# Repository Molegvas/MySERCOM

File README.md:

#          Адаптер силового блока зарядного устройства

##   Кратко 

Адаптер силового блока предназначен для соединения управляющего контроллера с силовым блоком. Центральный микроконтроллер освобождается от исполнения рутинных операций.

 ### Аппаратная поддержка
   Прототипирование выполнялось на плате SAMD21-M0-Mini. Подробности включения хорошо описаны в https://github.com/BLavery/SAMD21-M0-Mini.
  К сожалению поддержка Arduino не в полной мере соответствует потребностям проекта, но это преодолимо.

 #### Особенности прототипирования на плате SAMD21-M0-Mini
  В качестве инструкции:  https://github.com/BLavery/SAMD21-M0-Mini:
 * select the board: Tools/Board = Arduino SAMD / "Arduino Zero (Native USB Port)".
 * Double-click the board reset button. Upload. See if a LED blinks.
 explain a bit:
 1. The Arduino bootloader uses double click on reset button to enter flash upload mode. Single
    reset enters normal running mode.
 2. The serial/bossac mode of USB upload is included in the Arduino install.
 3. The regular user LED is missing. So we choose one of the TX/RX LEDs. For the moment, 
    the Arduino sketch is NOT otherwise driving these as TX/RX indicators (see above), 
    so we can re-employ them.
 4. But what pin or GPIO number? For this board, reference the pins as 0-26 or A0-A5. Not D25, 
    nor PB03 or PB3.

 ### Обмен между контроллерами.

*  Протокол WAKE является логическим уровнем интерфейса управления оборудованием с помощью асинхронного последовательного канала. Физический уровень интерфейса протоколом не определяется, может использоваться, например, RS-232, RS-485 или USB. Протокол позволяет производить обмен пакетами данных (data frames) длиной до 255 байт с адресуемыми устройствами, которых может быть до 127. Формат данных может быть любым. Могут передаваться байтовые поля, многобайтовые слова или строки символов. Для контроля правильности передачи данных используется контрольная сумма (CRC-8).
* Подробная информация о WAKE: http://leoniv.diod.club/articles/wake/wake.html
Выбор этого протокола объясняется тем, что хорошо известен автору и многолетней работой доказал свою надежность в устройстве ротации кондиционеров.
* Первоначальные планы использовать в качестве физического носителя SPI разбились о прозу жизни - в наличии не оказалось соответствующего адаптера USB-3SPI. Для целей прототипирования используется USB-UART терминал WakeUp! от Ридико Леонида Ивановича. Найдете в "resources".
* Передача параметров из нескольких байт: сначала старший, потом младшие.
* Время ожидания ответа ограничено 1000мс.  

 ### Управление измерениями.

 #### Измерение напряжения
   Измерение напряжения предполагается в диапазоне от -0,2В до +20,0В. Режим АЦП - дифференциальный. Опорное напряжение и усиление - выбор есть. Если получится реализовать вариант со сдвигом по напряжению на 200мВ минусовой клеммы, то обработка неправильной полярности подключения не потребует аппаратной поддержки. 

 #### Измерение тока
   Измерение тока в диапазоне от -16 до +16 ампер на токоизмерительном шунте укладывается в диапазон входного напряжения от -160 до +160мВ. Режим АЦП - дифференциальный. Пороги аварийного отключения не выставлялись.
 #### Измерение тока разряда
Зарезервировано. 
 #### Измерение температуры
Для датчика типа MF52 B 3950 NTC термистор 2% 10 kOm, последовательно резистор 10 kOm, запитан от 3,3в.
Параметры по умолчанию и задаваемые командой 0x57:

| bits | ref | gain | sampl | div | comp | offset | ser Ohm | nom Ohm |
|------|-----|------|-------|-----|------|--------|---------|---------|
|  01  |  00 |  00  |   03  |  04 |  00  |  0000  |  2710   |   2710  |

Ответ: код АЦП (2 байта) и значение температур, умноженное на 100.
Вычисления производятся по формуле Стейнхарта.

* Конфигурирование канала измерения состоит из параметров АЦП (разрядность, усреднение, см. страницы 853 и 862) и датчика (опорное напряжение, усиление, приборное смещение, коэффициент преобразования данных в физическую величину).
* В ответ контроллер отправляет пакет, содержащий байт ошибки (зарезервированная позиция), двухбайтный код АЦП и двухбайтное значение измеренной величины (для напряжения - в милливольтах).
* Команды такого типа скорее исследовательские, служащие для поиска оптимальных конфигураций.
* Выбор параметров, предложенных в datasheet ... как говорится, "не все йогурты одинаково полезны" ... 
* Аппаратное смещение задается отдельной командой, усиление - не исследовалось.      
* Ниже дано пояснение формата команды на примере конфигурирования измерителя напряжения.
```c++
// Настройка измерителя напряжения (код команды 0x55  'cmd_set_adc_bat')     
void doAdcBat()
{
    if( rxNbt == 10 )		  // Проверка получения полного пакета
  {
    uint8_t err           = 0x00;
    constexpr uint8_t prb = 0x00; // Измеритель напряжения, в [] - ориентировочные параметры
      // Задать все параметры измерителя [ 01 00 00 03 04 00 0000 12BA ]
    adcBits     [prb] = rxDat[0]; // Разрешение: 0x00(12), [0x01(16)], 0x02(10),  0x03(8)
    prbReference[prb] = rxDat[1]; // Опорное:   [0x00(1V)], 0x01(1/1.48VDDA),     0x02(1/2VDDA), 0x03(ExtA)
    prbGain     [prb] = rxDat[2]; // Усиление:  [0x00(X1)], 0x01(X2),  0x03(X4),  0x04(X8),      (X16), (DIV2)    
    adcSamples  [prb] = rxDat[3]; // Накопление: 0x00(1),   0x01(2),   0x02(4),  [0x03(8)],      0x04(16), ... 0x0a
    adcDivider  [prb] = rxDat[4]; // Делитель:   0x00(2^0), 0x01(2^1), 0x02(2^2), 0x03(2^3),    [0x04(2^4)]... 0x07
    refComp    = 0x01 & rxDat[5]; // 0/1: выкл/вкл аппаратное смещение АЦП
    prbOffset   [prb] = get16(6); // Приборное смещение: 0x8000 ... 0x7fff
    prbDivider  [prb] = get16(8); // Коэффициент преобразования в милливольты:   [0x12ba]
      // Считать результат
                                          // Нулевой байт - ошибка параметра (зарезервировано)
    txDat[1] = ( adcVoltage >> 8) & 0xFF; // Hi
    txDat[2] =   adcVoltage       & 0xFF; // Lo
    txDat[3] = ( voltage >> 8)    & 0xFF; // Hi
    txDat[4] =   voltage          & 0xFF; // Lo

    txReplay( 5, err );		  // Ответ из 5 байт
  }
  else
  {
    txReplay(1, err_tx);	  // Передается код ошибки протокола
  }
}
```

 ### Управление процессами
   Управление производится через два регистра состояния (они же и регистры управления)
 #### state1
* _switchStatus          - управление коммутатором в цепи плюсовой клеммы (foff_pin)
* _converterStatus       - управление преобразователем UC3845
* _currentControlStatus  - пид-регулирование по току
* _voltageControlStatus  - пид-регулирование по напряжению
* _chargeStatus          - управление переключением аналогового выхода на заряд или разряд
* _dischargeStatus       - состояние заряд/разряд
* _pauseStatus           - пауза
* _pidStatus        	 - управление регулятором

 #### state2
* _overHeatingStatus     - состояние перегрева
* _overloadStatus        - состояние перегрузки
* _powerLimitationStatus - состояние ограничения мощности
* _reversePolarityStatus - состояние "обратная полярность"
* _shortCircuitStatus    - состояние "короткое замыкание"
* _calibrationStatus     - состояние калибровки
* _upgradeStatus         - обновление
* _reserve2Status        - резерв 2

 ### Команды управления процессами
 * 0x60 - тестовая - управление коммутатором
 * 0x61 - тестовая - управление преобразователем
 * 0x62 - тестовая - прямое управление преобразователем по напряжению
 * 0x63 - тестовая - прямое управление преобразователем по току
 * 0x64 - 

 ### PID-регулирование.

  Для прототипирования выбран быстрый 32-битный пид-регулятор с фиксированной точкой для Arduino:
FastPID v1.3.1 by Mike Matera 
https://github.com/mike-matera/FastPID

  Этот пид-регулятор работает быстрее, поскольку он позволяет избежать дорогостоящих операций с плавающей запятой. Пид-регулятор сконфигурирован с коэффициентами с плавающей запятой и переводит их в фиксированную точку внутренне. Это накладывает ограничения на область применения коэффициентов. Установка условий I и D на ноль ускоряет работу регулятора. Регулятор сконфигурирован для работы на фиксированной частоте, и вызывающий код отвечает за работу на этой частоте. Параметры Ki и Kd масштабируются по частоте, чтобы сэкономить время во время операции step(). 

 #### Описание коэффициентов регулирования

  * Kp - пропорциональный 
  * Ki - интегральный 
  * Kd - дифференциальный 
  * Hz - частота выполнения контроллера 

#### Диапазон значений коэффициентов 

Конвейер вычислений ожидает 16-битные коэффициенты. Это контролируется PARAM_BITS и не должно быть изменено, иначе может возникнуть нежелательное переполнение. Количество битов до и после десятичного знака контролируется параметром PARAM_SHIFT в FastPID.h. значение по умолчанию для PARAM_SHIFT равно 8 и может быть изменено в соответствии с вашим приложением.

  * Диапазон параметра P от 0.00390625 до 255 включительно.** 
  * Параметр I равен P / Hz** 
  * Параметр D равен P * Hz** 
* ** До выяснения реальной потребности в диапазоне диапазон P установлен от 0,01 до 255.
Регулятор проверяет наличие нарушений диапазона параметров и не будет работать, если коэффициент находится вне диапазона. Все операции конфигурации возвращают bool, чтобы предупредить пользователя об ошибке. Функция err() проверяет состояние ошибки. Ошибки можно устранить с помощью функции clear().

#### Частота Выполнения

* ** Частота выполнения не определяется автоматически, это значительно повышает производительность регулятора. Вместо этого Ki и Kd масштабируются на этапе настройки. Очень важно вызывать step() с той скоростью, которую вы укажете. 

#### Вход и выход

Входной сигнал и заданное значение являются int16_t, что соответствует разрядности АЦП и позволяет разместить отрицательные показания и заданные значения. Выходные данные PID - это int16_t. Фактическая битовая ширина и знаковость вывода могут быть настроены. 
  
  * bits - выходная ширина будет ограничена значениями внутри этого битового диапазона. Допустимые значения от 1 до 16 
  * sign если true, то выходной диапазон равен от -2^(бит-1) до -2^(бит-1) -1. Если выходной диапазон false, то от 0 до 2^(бит-1)-1. 
  * ** Максимальное выходное значение контроллера -32767 (даже в 16-битном беззнаковом режиме) ** 

#### Исполнение

Производительность FastPID варьируется в зависимости от коэффициентов. Когда коэффициент равен нулю, выполняется меньший расчет. Проверено: менее 10мкс. 

#### ПРИКЛАДНОЙ ПРОГРАММНЫЙ ИНТЕРФЕЙС (API)
Здесь и далее приводится авторский текст из указанного первоисточника с незначительными изменениями.

API стремится быть простым и понятным. Я не буду имплицировать функции в регуляторе, которые были бы лучше реализованы вне его.
```c++
FastPID()
```
Создайте контроллер по умолчанию. Все коэффициенты по умолчанию равны нулю. Не используйте сконструированный по умолчанию контроллер до тех пор, пока вы не вызовете setCoefficients() и setOutputconfig()

```c++
FastPID(float kp, float ki, float kd, float hz, int bits=16, bool sign=false)
```
Постройте контроллер, который готов к работе. Вызывает следующие вызовы:
```c++
configure(kp, ki, kd, hz, bits, sign);

bool setCoefficients(float kp, float ki, float kd, float hz);
```
Настройка ПИД коэффициентов. Коэффициенты ki и kd масштабируются на величину hz. Значение hz информирует PID о скорости, которую вы назовете step(). Вызывающий код отвечает за вызов step() со скоростью в hz. Возвращает значение false, если произошла ошибка конфигурации. Что может быть связано с предыдущим вызовом.

bool setOutputConfig(int bits, bool sign);

Установите конфигурацию ouptut по битам/знаку. Диапазон выхода будет следующим:

Для знака, равного true  2^(n-1) - 1 вниз до -2^(n-1)

Для знака, равного false  2^n-1 вниз до 0

* ** bits равен 16-это особый случай. 
* ** Когда bits равен 16 и знак false диапазон выходных напряжений 32767 до 0

Возвращает значение false, если произошла ошибка конфигурации. Что может быть связано с предыдущим вызовом.
```c++
bool setOutputRange (int16_t min, int16_t max);
```
Установите диапазон ouptut непосредственно. Эффективный диапазон действия составляет:

* Мин:  от -32768 до 32766
* Макс: от -32767 до 32767

Min должно быть больше, чем max.

Возвращает значение false, если произошла ошибка конфигурации. Что может быть связано с предыдущим вызовом.
```c++
void clear();
```
Перезагрузите контроллер. Это должно быть сделано до того, как вы каким-либо образом измените конфигурацию.
```c++
bool configure(float kp, float ki, float kd, float hz, int bits=16, bool sign=false);
```
Массовая настройка контроллера. Эквивалентный:
```c++
clear();
setCoefficients(kp, ki, kd, hz);
setOutputConfig(bits, sign);

int16_t step(int16_t sp, int16_t fb);
```
Выполните один шаг контроллера и верните следующий вывод.
```c++
bool err();
```
Проверьте наличие ошибки конфиурации. Контроллер не будет работать, если эта функция возвращает true. 

#### Целочисленный Завод 

Приложения, которые управляют медленно движущимися системами и имеют ненулевой интегральный член, часто видят значительное превышение при запуске. 
Это вызвано интегральной суммой winidng up, поскольку она помнит долгое время вдали от заданной точки. Если это описывает вашу систему есть две вещи, которые вы можете сделать. 

##### Заводную решение: ограничить сумму 

В FastPID есть константы.h, которые контролируют максимально допустимый Интеграл. Понижение этих параметров предотвращает выход контроллера из строя. 
запоминание как можно большего смещения от заданного значения и позволит уменьшить превышение. 
```c++
#define INTEG_MAX    (INT32_MAX)
#define INTEG_MIN    (INT32_MIN)
```
Меняйте эти константы с осторожностью. Установка их слишком низко исправит вашу проблему превышения скорости, но это негативно скажется на способность регулятора регулировать нагрузку. Если вы не уверены в правильной константе используйте следующее решение вместо этого ограничения суммы. 

#### Ограничение Заводки: Ограниченное Регулирование 

Пид-контроллер лучше всего работает, когда система находится близко к заданному значению. Во время фазы запуска или в случае с a 
значительная экскурсия, вы можете полностью отключить пид-контроль. Пример этого можно найти в контроллере Sous-Vide 
пример в этом проекте. Ядро логики находится в этом коде: 
```c++
if (feedback < (setpoint * 0.9)) {
  analogWrite(PIN_OUTPUT, 1);
  myPID.clear();
}
else {
  analogWrite(PIN_OUTPUT, myPID.step(setpoint, feedback));
}
```
Код обходит ПИД, когда температура составляет менее 90% от заданного значения, просто включив нагреватель. Когда 
температура выше 90% от заданного значения пид включен. Фиксация вашего промаха таким образом дает вам гораздо лучший контроль
вашей системы без необходимости добавлять сложные, недопустимые и трудные для понимания функции к пид-контроллеру.

#### Sample Code 
```c++
#include <FastPID.h>

#define PIN_INPUT     A0
#define PIN_SETPOINT  A1
#define PIN_OUTPUT    9

float Kp=0.1, Ki=0.5, Kd=0.1, Hz=10;
int output_bits = 8;
bool output_signed = false;

FastPID myPID(Kp, Ki, Kd, Hz, output_bits, output_signed);

void setup()
{
  Serial.begin(9600);
  if (myPID.err()) {
    Serial.println("There is a configuration error!");
    for (;;) {}
  }
}

void loop()
{
  int setpoint = analogRead(PIN_SETPOINT) / 2; 
  int feedback = analogRead(PIN_INPUT);
  int ts = micros();
  uint8_t output = myPID.step(setpoint, feedback);
  int tss = micros();
  analogWrite(PIN_OUTPUT, output);
  Serial.print("(Fast) micros: "); 
  Serial.print(tss - ts);
  Serial.print(" sp: "); 
  Serial.print(setpoint); 
  Serial.print(" fb: "); 
  Serial.print(feedback);
  Serial.print(" out: ");
  Serial.println(output);
  delay(100);
}
```
### Справочная информация (подлежит уточнению)

|  код  |          имя            |            параметры            |           пример (данные, hex)            |
|-------|-------------------------|---------------------------------|-------------------------------------------|
| ответ	| 			  | cmd_err  			    | ошибка приема пакета                      |

#### Команды АЦП-преобразований

|  код  |          имя            |            параметры            |           пример (данные, hex)            |
|-------|-------------------------|---------------------------------|-------------------------------------------|
| 0x50	| cmd_adc_read_probes     |                                 |                                           |
| ответ	| 			  | adcU_h,l, adcI_h,l, 	    | 1F 00 1F 00                               |
|    	| 			  | adcD_h,l, adcC_h,l,             | 1F 00 1F 00                               |
|       |                         | mcr1, mcr2                      | 00 FF                                     |
| 0x52	| cmd_adc_config52        | nPrb, gain, ref, offset, mult   | 01 00 02 00 00 01 00                      |
| ответ	| 			  |                                 | 00                                        |
| 0x53	| cmd_adc_config53        | nPrb, bits, samples, divider    | 01 01 02 03                               |
| ответ	| 			  |                                 | 00                                        |
|       |                         |                                 |                                           | 

#### Команды ПИД-регулятора

|  код  |          имя            |            параметры            |           пример (данные, hex)            |
|-------|-------------------------|---------------------------------|-------------------------------------------|
| 0x40	| cmd_pid_configure       | kp, ki, kd, hz, bits, sign      | 00 19 00 80 00 00 0A 00 00 0A 00          |
| ответ	| 			  | 00 / 0x40                       | OK / ошибка параметра                     |
| 0x41	| cmd_pid_coefficients    | kp, ki, kd, hz                  | 00 19 00 80 00 00 0A 00                   |
| ответ	| 			  | 00 / 0x40                       | OK / ошибка параметра                     |
| 0x42	| cmd_pid_output_range    | min, max                        | 00 00 03 FF                               |
| ответ	| 			  | 00 / 0x40                       | OK / ошибка параметра                     |
| 0x43	| cmd_pid_output_config   | bits, sign                      | 10 00                                     |
| ответ	| 			  | 00 / 0x40                       | OK / ошибка параметра                     |
| 0x44	| cmd_pid_clear           |                                 |                                           |
| ответ	| 			  | 00 / 0x40                       | OK / ошибка параметра                     |
| 0x45	| cmd_pid_stop_go         | (стоп-пауза-пуск)               |                                           |
| ответ	| 			  | 00 / 0x40                       | OK / ошибка                               |
| 0x46	| cmd_pid_test            | res, mode, setpoint, min, max   | FF 03 01 FF 00 00 03 FF                   |
| ответ	| 			  | 00 / 0x40                       | OK / ошибка параметра                     |
| 0x47	|                         |                                 |                                           |
|       |                         |                                 |                                           | 
* kp, ki, kd, hz - целочисленные, полученные умножением на 256 (т.е << 8)

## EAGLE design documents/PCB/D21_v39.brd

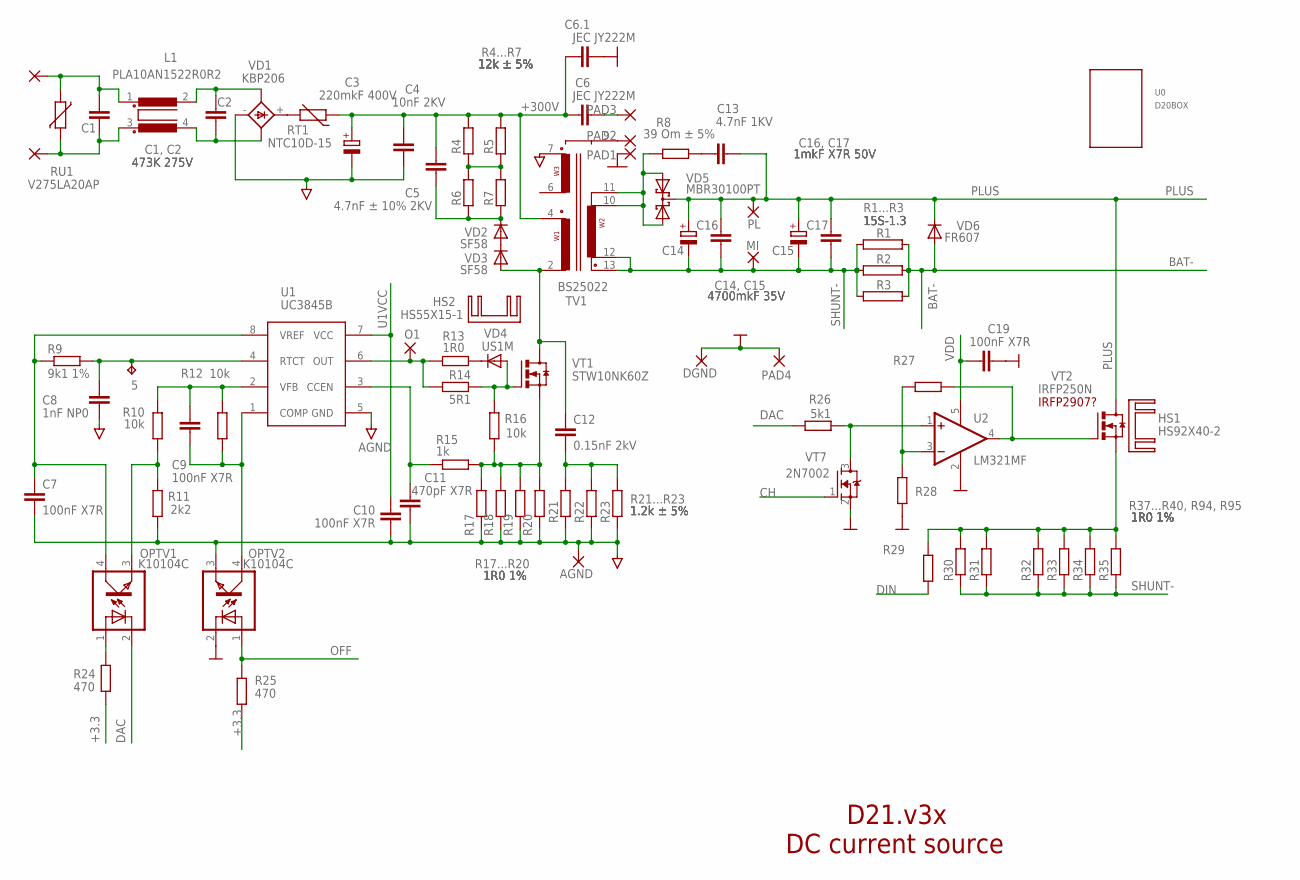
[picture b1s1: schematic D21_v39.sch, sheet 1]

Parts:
5: TPB1,27; B1,27
AGND: WIREPAD4,16O1,6; 4,16O1,6
C1, C2: 473K 275V; C150-054X183
C3: 220mkF 400V; EB25D
C4: 10nF 2KV; C102-043X133
C5: 4.7nF ± 10% 2KV; C102-064X133
C6, C6.1: JEC JY222M; C102-064X133
C7, C9, C19: 100nF X7R; C0603
C8: 1nF NP0; C0603
C10: 100nF X7R; C0805
C11: 470pF X7R; C0603
C12: 0.15nF 2kV; C075-032X103
C13: 4.7nF 1KV; C102-064X133
C14, C15: 4700mkF 35V; E7,5-18
C16, C17: 1mkF X7R 50V; C0805
DGND: WIREPAD4,16O1,6; 4,16O1,6
HS1: HS92X40-2; YS92X40
HS2: HS55X15-1; HS55X15
L1: PLA10AN1522R0R2; DK30
MI: WIREPAD4,16O1,6; 4,16O1,6
O1: WIREPAD1,6/0,8; 1,6/0,8
OPTV1, OPTV2: K10104C; SMD4-7
PAD1, PAD2, PAD3: SMD2; SMD1,27-2,54
PAD4: WIREPAD4,16O1,6; 4,16O1,6
PL: WIREPAD4,16O1,6; 4,16O1,6
R1, R2, R3: 15S-1.3
R4, R5, R6, R7: 12k ± 5%; 0515/20
R8: 39 Om ± 5%; 0515/20
R9: 9k1 1%; R0603
R10, R12, R16: 10k; R0603
R11: 2k2; R0603
R13: 1R0; R0805
R14: 5R1; R0805
R15: 1k; R0603
R17, R18, R19, R20, R30, R31, R32, R33, R34, R35: 1R0 1%; R2512
R21, R22, R23: 1.2k ± 5%; 0515/20
R24, R25: 470; R0603
R26: 5k1; R0603
R27, R28, R29: R-EU_R0603; R0603
RT1: NTC10D-15; NTC15
RU1: V275LA20AP; S10K11-H
TV1: BS25022
U0: D20BOX
U1: UC3845B; SO08
U2: LM321MF; SOT23-5
VD1: KBP206; 2KBP
VD2, VD3: SF58; DO201-15
VD4: US1M; SMADIODE
VD5: MBR30100PT; TO-247AD-V
VD6: FR607; P6-15
VT1: STW10NK60Z; TO-247AD-V
VT2: IRFP250N; TO-247AD-V
VT7: 2N7002; SOT23-R
X1: 220VAC

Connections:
10-11: R8.1, TV1.10, TV1.11, VD5.G (A1), VD5.S (A2)
+3.3: R24.2, R25.2; also elsewhere on the board
+300V: C3.+, C4.1, C5.1, C6.1, C6.1.1, R4.2, R5.2, RT1.1, TV1.4; also elsewhere on the board
AGND: AGND.1, C3.-, C4.2, C7.2, C8.2, C10.2, C11.2, OPTV2.3 (EMIT), R11.1, R17.1, R18.1, R19.1, R20.1, R21.1, R22.1, R23.1, TV1.7, U1.5 (GND), VD1.-; also elsewhere on the board
BAT-: R1.2, R2.2, R3.2, VD6.A; also elsewhere on the board
CH: VT7.1 (G); also elsewhere on the board
DAC: OPTV1.2 (C), R26.2; also elsewhere on the board
DIN: R29.2; also elsewhere on the board
DIN1: R29.1, R30.2, R31.2, R32.2, R33.2, R34.2, R35.2, VT2.S
GND: C6.1.2, C19.1, DGND.1, OPTV2.2 (C), PAD1.1, PAD4.1, R28.2, U2.2 (V-), VT7.2 (S); also elsewhere on the board
HS2: C5.2, R6.1, R7.1, VD2.C
unnamed: R4.1, R5.1, R6.2, R7.2
unnamed: VD2.A, VD3.C
unnamed: C12.1, TV1.2, VD3.A, VT1.D
unnamed: C12.2, R21.2, R22.2, R23.2
unnamed: C1.2, L1.3, RU1.2, X1.P$2 (2)
unnamed: RT1.2, VD1.+
unnamed: R14.2, R16.2, VD4.A, VT1.G
unnamed: PAD2.1, TV1.9
unnamed: R15.2, R16.1, R17.2, R18.2, R19.2, R20.2, VT1.S
unnamed: C2.1, L1.2, VD1.AC1
unnamed: C1.1, L1.1, RU1.1, X1.P$1 (1)
unnamed: C2.2, L1.4, VD1.AC2
unnamed: O1.1, R13.1, R14.1, U1.6 (OUT)
unnamed: R13.2, VD4.C
unnamed: OPTV1.1 (A), R24.1
unnamed: C11.1, R15.1, U1.3 (CCEN)
unnamed: C9.2, OPTV2.4 (COL), R12.1, U1.1 (COMP)
unnamed: C9.1, R10.2, R12.2, U1.2 (VFB)
unnamed: OPTV1.3 (EMIT), R10.1, R11.2
unnamed: C7.1, OPTV1.4 (COL), R9.1, U1.8 (VREF)
unnamed: 5.TP, C8.1, R9.2, U1.4 (RTCT)
unnamed: R27.1, U2.4 (OUT), VT2.G
unnamed: R27.2, R28.1, U2.3 (-IN)
unnamed: R26.1, U2.1 (+IN), VT7.3 (D)
unnamed: C6.2, PAD3.1
unnamed: C13.1, R8.2
OFF: OPTV2.1 (A), R25.1; also elsewhere on the board
PLUS: C13.2, C14.+, C15.+, C16.1, C17.1, PL.1, VD5.D (C), VD6.C, VT2.D; also elsewhere on the board
SHUNT-: C14.-, C15.-, C16.2, C17.2, MI.1, R1.1, R2.1, R3.1, R30.1, R31.1, R32.1, R33.1, R34.1, R35.1, TV1.12, TV1.13; also elsewhere on the board
U1VCC: C10.1, U1.7 (VCC); also elsewhere on the board
VDD: C19.2, U2.5 (V+); also elsewhere on the board

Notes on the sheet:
D21.v3x DC current source
R4...R7
R21...R23
R17...R20
R37...R40, R94, R95
C16, C17
C14, C15
R1...R3
C1, C2
IRFP2907?

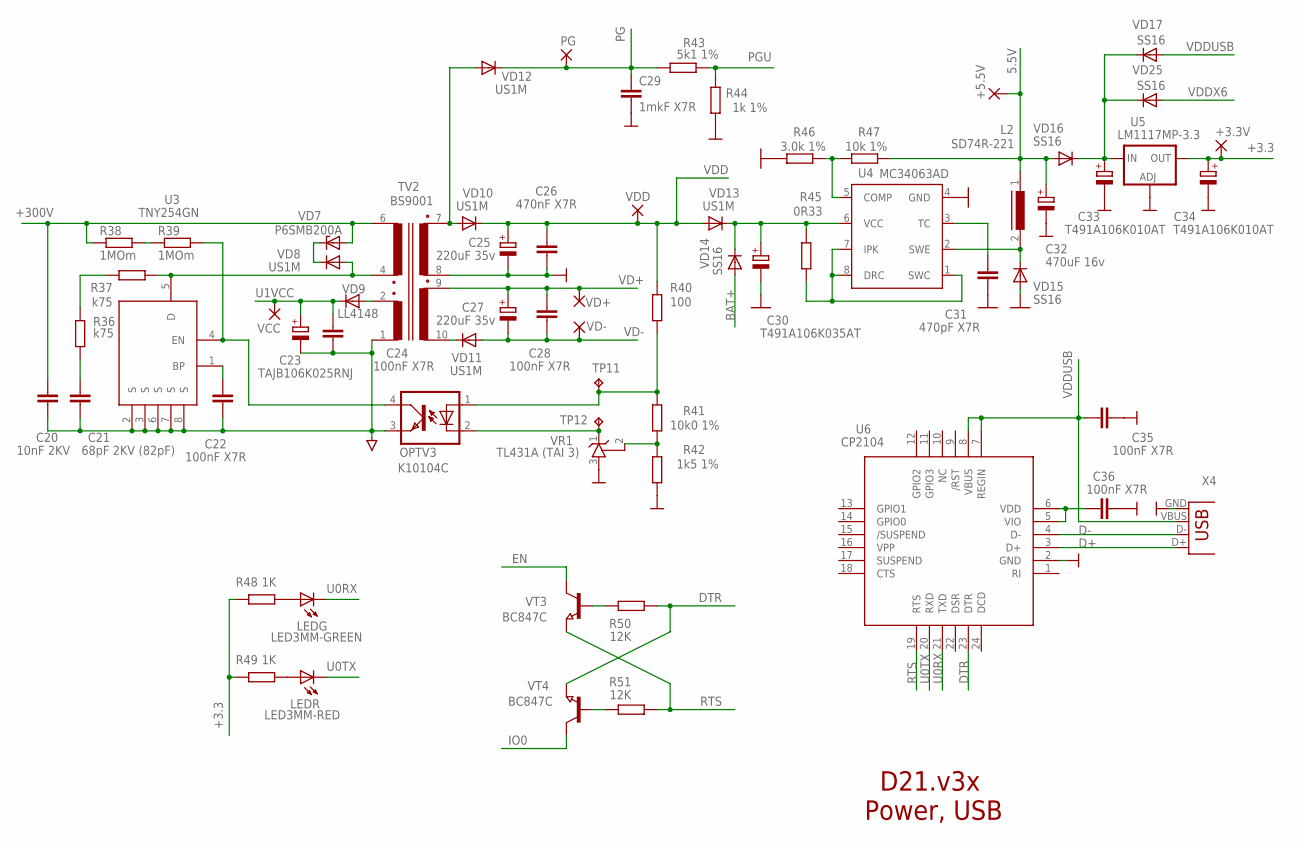
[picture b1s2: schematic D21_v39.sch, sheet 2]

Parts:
+3.3V, +5.5V: WIREPAD1,6/0,8; 1,6/0,8
C20: 10nF 2KV; C102-043X133
C21: 68pF 2KV (82pF); C050-024X044
C22, C24, C35, C36: 100nF X7R; C0603
C23: TAJB106K025RNJ; CT6032
C25, C27: 220uF 35v; E3,5-8
C26: 470nF X7R; C0805
C28: 100nF X7R; C0805
C29: 1mkF X7R; C0805
C30: T491A106K035AT; CT6032
C31: 470pF X7R; C0603
C32: 470uF 16v; E5-8,5
C33, C34: T491A106K010AT; CT3216
L2: SD74R-221; DR74
LEDG: LED3MM-GREEN; LED3MM-H7MMG
LEDR: LED3MM-RED; LED3MM-H7MMR
OPTV3: K10104C; SMD4-7
PG: WIREPAD1,6/0,8; 1,6/0,8
R36, R37: k75; R1206
R38, R39: 1MOm; R1206
R40: 100; R0603
R41: 10k0 1%; R0603
R42: 1k5 1%; R0603
R43: 5k1 1%; R0603
R44: 1k 1%; R0603
R45: 0R33; R0603
R46: 3.0k 1%; R0603
R47: 10k 1%; R0603
R48, R49: 1K; R0603
R50, R51: 12K; R0603
TP11, TP12: TPB1,27; B1,27
TV2: BS9001
U3: TNY254GN; SMD-8
U4: MC34063AD; SO08
U5: LM1117MP-3.3; SOT223-W
U6: CP2104; QFN-24
VCC: WIREPAD1,6/0,8; 1,6/0,8
VD7: P6SMB200A; SMB
VD8, VD10, VD11, VD12, VD13: US1M; SMADIODE
VD9: LL4148; SOD80C
VD14, VD15, VD16, VD17, VD25: SS16; SMADIODE
VD+: WIREPAD1,6/0,8; 1,6/0,8
VD-: WIREPAD1,6/0,8; 1,6/0,8
VDD: WIREPAD1,6/0,8; 1,6/0,8
VR1: TL431A (TAI 3); SOT23
VT3, VT4: BC847C; SOT23
X4: USB-B; USB-B-H

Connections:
5.5V: +5.5V.1, C32.+, L2.1, R47.2, VD16.A; also elsewhere on the board
+3.3: +3.3V.1, C34.+, R48.2, R49.2, U5.2 (OUT); also elsewhere on the board
+300V: C20.1, R38.1, TV2.6, VD7.A; also elsewhere on the board
AGND: C20.2, C21.2, C22.2, C23.-, C24.2, OPTV3.3 (EMIT), TV2.1, U3.2 (S), U3.3 (S), U3.6 (S), U3.7 (S), U3.8 (S); also elsewhere on the board
BAT+: VD14.A; also elsewhere on the board
D+: U6.3 (D+), X4.D+
D-: U6.4 (D-), X4.D-
DTR: R50.2, U6.23 (DTR), VT4.2 (E)
EN: VT3.3 (C); also elsewhere on the board
GND: C25.-, C26.2, C29.2, C30.-, C31.2, C32.-, C33.-, C34.-, C35.2, C36.2, R42.2, R44.1, R46.1, TV2.8, U4.4 (GND), U5.1 (ADJ), U6.2 (GND), VD15.A, VR1.3 (A), X4.GND; also elsewhere on the board
IO0: VT4.3 (C); also elsewhere on the board
unnamed: R36.2, R37.1
unnamed: C36.1, U6.5 (VIO), U6.6 (VDD)
unnamed: R37.2, TV2.4, U3.5 (D), VD8.A
unnamed: C21.1, R36.1
unnamed: C22.1, U3.1 (BP)
unnamed: R38.2, R39.1
unnamed: OPTV3.4 (COL), R39.2, U3.4 (EN)
unnamed: OPTV3.1 (A), R40.2, R41.1, TP11.TP
unnamed: TV2.2, VD9.A
unnamed: VD7.C, VD8.C
unnamed: TV2.10, VD11.C
unnamed: TV2.7, VD10.A, VD12.A
unnamed: C30.+, R45.1, U4.6 (VCC), VD13.C, VD14.C
unnamed: LEDR.A, R49.1
unnamed: LEDG.A, R48.1
unnamed: R45.2, U4.1 (SWC), U4.7 (IPK), U4.8 (DRC)
unnamed: L2.2, U4.2 (SWE), VD15.C
unnamed: C31.1, U4.3 (TC)
unnamed: R46.2, R47.1, U4.5 (COMP)
unnamed: C33.+, U5.3 (IN), VD16.C, VD17.C, VD25.C
unnamed: R41.2, R42.1, VR1.2 (R)
unnamed: R51.1, VT4.1 (B)
unnamed: R50.1, VT3.1 (B)
unnamed: OPTV3.2 (C), TP12.TP, VR1.1 (C)
PG: C29.1, PG.1, R43.1, VD12.C; also elsewhere on the board
PGU: R43.2, R44.2; also elsewhere on the board
RTS: R51.2, U6.19 (RTS), VT3.2 (E)
U0RX: LEDG.K (C), U6.21 (TXD); also elsewhere on the board
U0TX: LEDR.K (C), U6.20 (RXD); also elsewhere on the board
U1VCC: C23.+, C24.1, VCC.1, VD9.C; also elsewhere on the board
VD+: C27.+, C28.1, TV2.9, VD+.1; also elsewhere on the board
VD-: C27.-, C28.2, VD11.A, VD-.1; also elsewhere on the board
VDD: C25.+, C26.1, R40.1, VD10.C, VD13.A, VDD.1; also elsewhere on the board
VDDUSB: C35.1, U6.7 (REGIN), U6.8 (VBUS), VD17.A, X4.VBUS
VDDX6: VD25.A; also elsewhere on the board

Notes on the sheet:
D21.v3x Power, USB

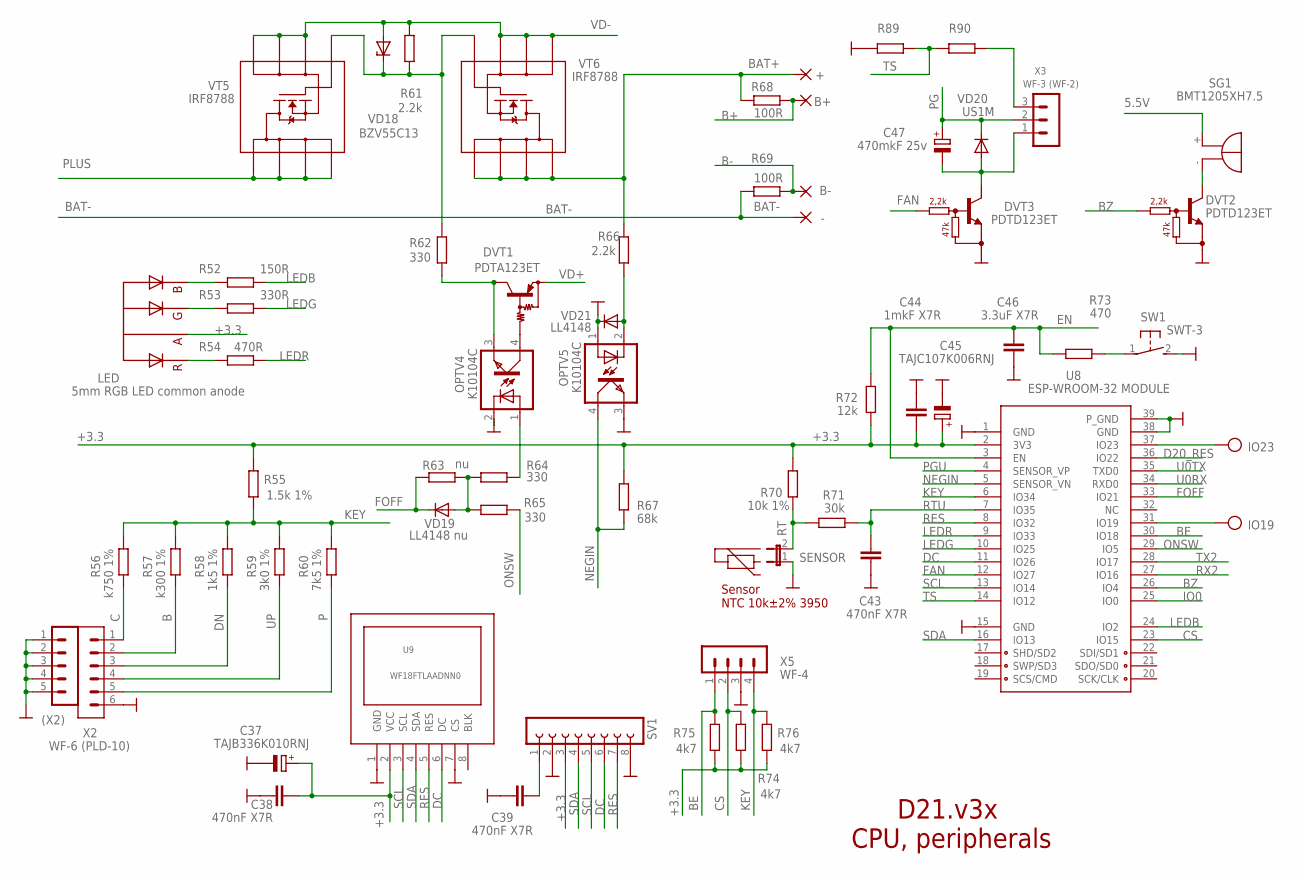
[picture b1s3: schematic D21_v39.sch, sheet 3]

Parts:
(X2): MA05-1
+: +; WIREPAD8_3
-: -; WIREPAD8_3
B+: WIREPAD4,16O1,6; 4,16O1,6
B-: WIREPAD4,16O1,6; 4,16O1,6
C37: TAJB336K010RNJ; CT6032
C38, C39, C43: 470nF X7R; C0805
C44: 1mkF X7R; C0805
C45: TAJC107K006RNJ; CT3528
C46: 3.3uF X7R; C0603
C47: 470mkF 25v; E3,5-8
DVT1: PDTA123ET; SC59-BEC
DVT2, DVT3: PDTD123ET; SOT23-BEC
IO19, IO23: TESTPOINTROUND1MM; TESTPOINT_ROUND_1MM
LED: 5mm RGB LED common anode; LED5MMRGB
OPTV4, OPTV5: K10104C; SMD4-7
R52: 150R; R0603
R53: 330R; R0603
R54: 470R; R0603
R55: 1.5k 1%; R0603
R56: k750 1%; R0603
R57: k300 1%; R0603
R58: 1k5 1%; R0603
R59: 3k0 1%; R0603
R60: 7k5 1%; R0603
R61, R66: 2.2k; R0603
R62, R64, R65: 330; R0603
R63: nu; R0603
R67: 68k; R0603
R68, R69: 100R; R0603
R70: 10k 1%; R0603
R71: 30k; R0603
R72: 12k; R0603
R73: 470; R0603
R74, R75, R76: 4k7; R0603
R89, R90: R-EU_R0603; R0603
SENSOR: JP1E; JP1
SG1: BMT1205XH7.5
SV1: FE08-1; FE08
SW1: SWT-3; B3F-31XX
U8: ESP-WROOM-32 MODULE; ESP-WROOM-32MORO
U9: WF18FTLAADNN0; TFT_1_8
VD18: BZV55C13; SOD80C
VD19: LL4148 nu; SOD80C
VD20: US1M; SMADIODE
VD21: LL4148; SOD80C
VT5, VT6: IRF8788; SO-8
X2: WF-6 (PLD-10); WF-6
X3: WF-3 (WF-2); WF-3
X5: WF-4

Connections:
5.5V: SG1.+; also elsewhere on the board
+3.3: C37.+, C38.1, C44.1, C45.+, LED.P$3 (A), R55.2, R67.1, R70.1, R72.1, R74.1, R75.1, R76.1, SV1.3, U8.2 (3V3), U9.2 (VCC); also elsewhere on the board
B: R57.1, X2.2
B+: B+.1, R68.1; also elsewhere on the board
B-: B-.1, R69.1; also elsewhere on the board
BAT+: +.P$1, R66.1, R68.2, VT6.5 (D), VT6.6 (D), VT6.7 (D), VT6.8 (D); also elsewhere on the board
BAT-: -.P$1, R69.2; also elsewhere on the board
BE: R75.2, U8.30 (IO18), X5.1
BLK: U9.8 (BLK)
BZ: DVT2.B, U8.26 (IO4)
C: R56.2, X2.1
CS: R74.2, U8.23 (IO15), X5.2
D20_RES: U8.36 (IO22); also elsewhere on the board
DC: SV1.6, U8.11 (IO26), U9.6 (DC)
DN: R58.1, X2.3
EN: C46.2, R72.2, R73.1, U8.3 (EN); also elsewhere on the board
FAN: DVT3.B, U8.12 (IO27)
FOFF: R63.1, U8.33 (IO21), VD19.C; also elsewhere on the board
G: R61.1, R62.1, VD18.C, VT5.4 (G), VT6.4 (G)
GND: (X2).1, (X2).2, (X2).3, (X2).4, (X2).5, C37.-, C38.2, C39.2, C43.2, C44.2, C45.-, C46.1, DVT2.E, DVT3.E, OPTV4.2 (C), OPTV5.1 (A), OPTV5.3 (EMIT), R89.2, SENSOR.1, SV1.2, SV1.8, SW1.2 (S), U8.1 (GND), U8.15 (GND), U8.38 (GND), U8.39 (P_GND), U9.1 (GND), U9.7 (CS), VD21.C, X2.6, X5.3; also elsewhere on the board
IO0: U8.25 (IO0); also elsewhere on the board
KEY: R55.1, R56.1, R57.2, R58.2, R59.2, R60.1, R76.2, U8.6 (IO34), X5.4
LEDB: R52.1, U8.24 (IO2)
LEDG: R53.1, U8.10 (IO25)
LEDR: R54.1, U8.9 (IO33)
unnamed: R90.1, X3.3
unnamed: C39.1, SV1.1
unnamed: DVT2.C, SG1.-
unnamed: LED.P$2 (GREEN), R53.2
unnamed: LED.P$1 (BLUE), R52.2
unnamed: LED.P$4 (RED), R54.2
unnamed: C47.-, DVT3.C, VD20.A, X3.1
unnamed: DVT1.C, OPTV4.3 (EMIT), R62.2
unnamed: DVT1.B, OPTV4.4 (COL)
unnamed: OPTV5.2 (C), R66.2, VD21.A
unnamed: R63.2, R64.1, R65.2, VD19.A
unnamed: IO23.P$1, U8.37 (IO23)
unnamed: IO19.P$1, U8.31 (IO19)
unnamed: R73.2, SW1.1
NEGIN: OPTV5.4 (COL), R67.2, U8.5 (SENSOR_VN)
ONSW: R65.1, U8.29 (IO5)
P: R60.2, X2.5
PG: C47.+, VD20.C, X3.2; also elsewhere on the board
PGU: U8.4 (SENSOR_VP); also elsewhere on the board
PLUS: VT5.5 (D), VT5.6 (D), VT5.7 (D), VT5.8 (D); also elsewhere on the board
RES: SV1.7, U8.8 (IO32), U9.5 (RES)
RT: R70.2, R71.1, SENSOR.2
RTU: C43.1, R71.2, U8.7 (IO35); also elsewhere on the board
RX2: U8.27 (IO16); also elsewhere on the board
SCL: SV1.5, U8.13 (IO14), U9.3 (SCL)
SDA: SV1.4, U8.16 (IO13), U9.4 (SDA)
TOV2: OPTV4.1 (A), R64.2
TS: R89.1, R90.2, U8.14 (IO12)
TX2: U8.28 (IO17); also elsewhere on the board
U0RX: U8.34 (RXD0); also elsewhere on the board
U0TX: U8.35 (TXD0); also elsewhere on the board
UP: R59.1, X2.4
VD+: DVT1.E; also elsewhere on the board
VD-: R61.2, VD18.A, VT5.1 (S), VT5.2 (S), VT5.3 (S), VT6.1 (S), VT6.2 (S), VT6.3 (S); also elsewhere on the board

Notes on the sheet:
Sensor NTC 10k±2% 3950
D21.v3x CPU, peripherals

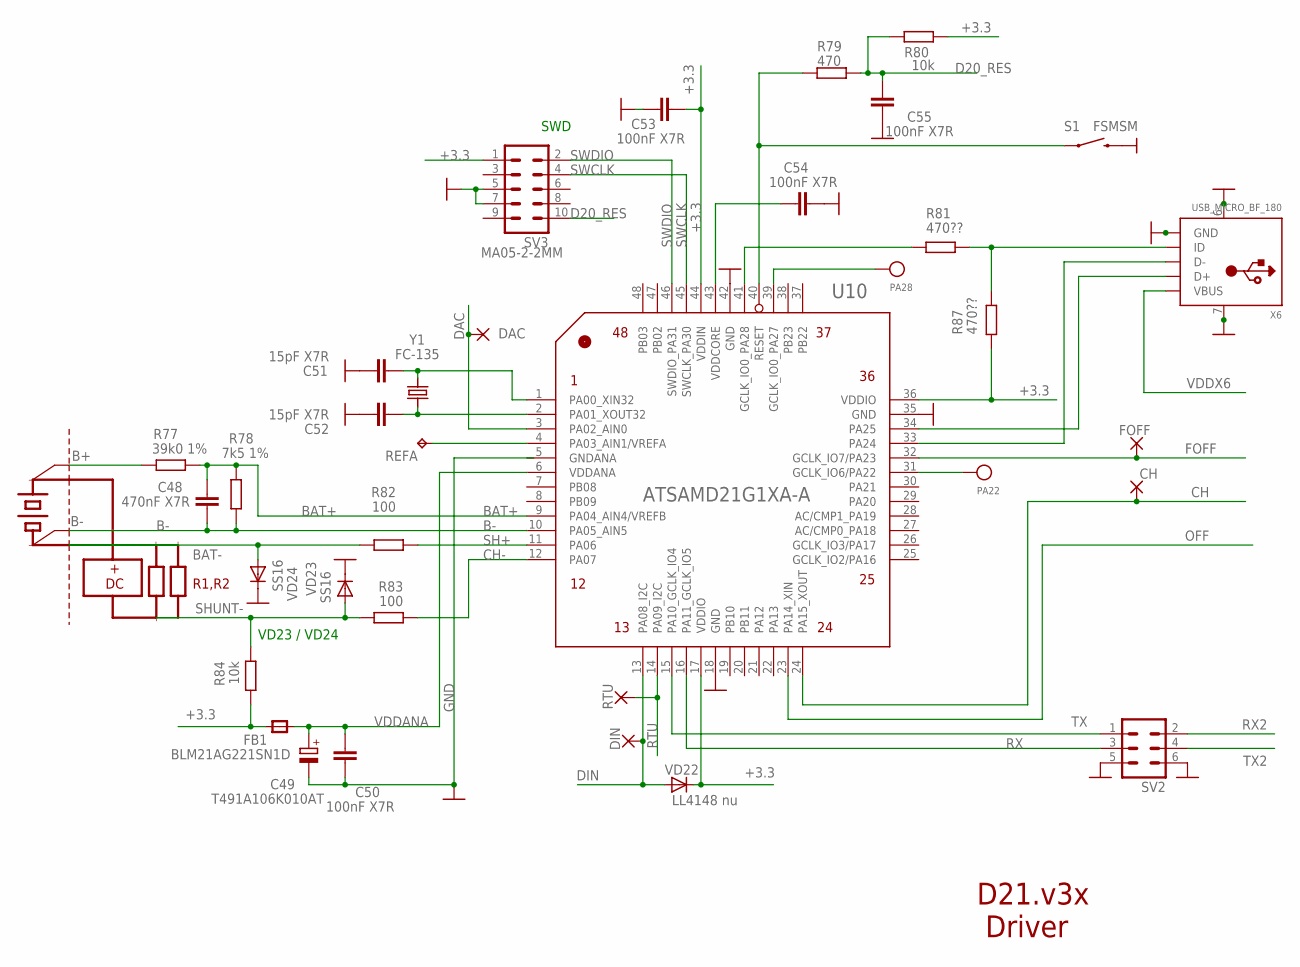
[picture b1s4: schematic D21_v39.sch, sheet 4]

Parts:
C48: 470nF X7R; C0805
C49: T491A106K010AT; CT3216
C50, C53, C54: 100nF X7R; C0603
C51, C52: 15pF X7R; C0603
C55: 100nF X7R; C0805
CH: WIREPAD1,6/0,8; 1,6/0,8
DAC: WIREPAD1,6/0,8; 1,6/0,8
DIN: WIREPAD1,6/0,8; 1,6/0,8
FB1: BLM21AG221SN1D; 0805
FOFF: WIREPAD1,6/0,8; 1,6/0,8
PA22, PA28: TESTPOINTROUND1MM; TESTPOINT_ROUND_1MM
R77: 39k0 1%; R0603
R78: 7k5 1%; R0603
R79: 470; R0603
R80, R84: 10k; R0603
R81, R87: 470??; R0603
R82, R83: 100; R0603
REFA: TPB1,27; B1,27
RTU: WIREPAD1,6/0,8; 1,6/0,8
S1: FSMSM; TACTILE-SWITCH-1101NE
SV2: MA03-2
SV3: MA05-2-2MM; MA5-2-2MM
U10: ATSAMD21G1XA-A; LQFP48_W
VD22: LL4148 nu; SOD80C
VD23, VD24: SS16; SMADIODE
X6: USB_MICRO_BF_180; USB_MICRO_180
Y1: FC-135; SMD03215C2

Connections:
+3.3: C53.1, FB1.1, R80.2, R84.2, R87.1, SV3.1, U10.17 (VDDIO), U10.36 (VDDIO), U10.44 (VDDIN), VD22.C; also elsewhere on the board
B+: R77.2; also elsewhere on the board
B-: C48.2, R78.2, U10.10 (PA05_AIN5); also elsewhere on the board
BAT+: C48.1, R77.1, R78.1, U10.9 (PA04_AIN4/VREFB); also elsewhere on the board
BAT-: R82.2, VD24.A; also elsewhere on the board
CH: CH.1, U10.24 (PA15_XOUT); also elsewhere on the board
CH-: R83.1, U10.12 (PA07)
D20_RES: C55.2, R79.2, R80.1, SV3.10; also elsewhere on the board
DAC: DAC.1, U10.3 (PA02_AIN0); also elsewhere on the board
DIN: DIN.1, U10.13 (PA08_I2C), VD22.A; also elsewhere on the board
FOFF: FOFF.1, U10.32 (GCLK_IO7/PA23); also elsewhere on the board
GND: C49.-, C50.2, C51.2, C52.2, C53.2, C54.1, C55.1, S1.P$2 (2), SV2.5, SV2.6, SV3.5, SV3.7, U10.5 (GNDANA), U10.18 (GND), U10.35 (GND), U10.42 (GND), VD23.C, VD24.C, X6.5 (GND), X6.6, X6.7; also elsewhere on the board
unnamed: R79.1, S1.P$1 (1), U10.40 (RESET)
unnamed: C52.1, U10.2 (PA01_XOUT32), Y1.P$1 (1)
unnamed: REFA.TP, U10.4 (PA03_AIN1/VREFA)
unnamed: C51.1, U10.1 (PA00_XIN32), Y1.P$2 (2)
unnamed: U10.33 (PA24), X6.2 (D-)
unnamed: U10.34 (PA25), X6.3 (D+)
unnamed: R81.2, R87.2, X6.4 (ID)
unnamed: PA28.P$1, U10.39 (GCLK_IO0_PA27)
unnamed: PA22.P$1, U10.31 (GCLK_IO6/PA22)
OFF: U10.23 (PA14_XIN); also elsewhere on the board
PA28: R81.1, U10.41 (GCLK_IO0_PA28)
RTU: RTU.1, U10.14 (PA09_I2C); also elsewhere on the board
RX: SV2.3, U10.16 (PA11_GCLK_IO5)
RX2: SV2.2; also elsewhere on the board
SH+: R82.1, U10.11 (PA06)
SHUNT-: R83.2, R84.1, VD23.A; also elsewhere on the board
SWCLK: SV3.4, U10.45 (SWCLK_PA30)
SWDIO: SV3.2, U10.46 (SWDIO_PA31)
TX: SV2.1, U10.15 (PA10_GCLK_IO4)
TX2: SV2.4; also elsewhere on the board
VDDANA: C49.+, C50.1, FB1.2, U10.6 (VDDANA)
VDDCORE: C54.2, U10.43 (VDDCORE)
VDDX6: X6.1 (VBUS); also elsewhere on the board

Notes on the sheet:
D21.v3x Driver
R1,R2
SWD
+ DC
VD23 / VD24

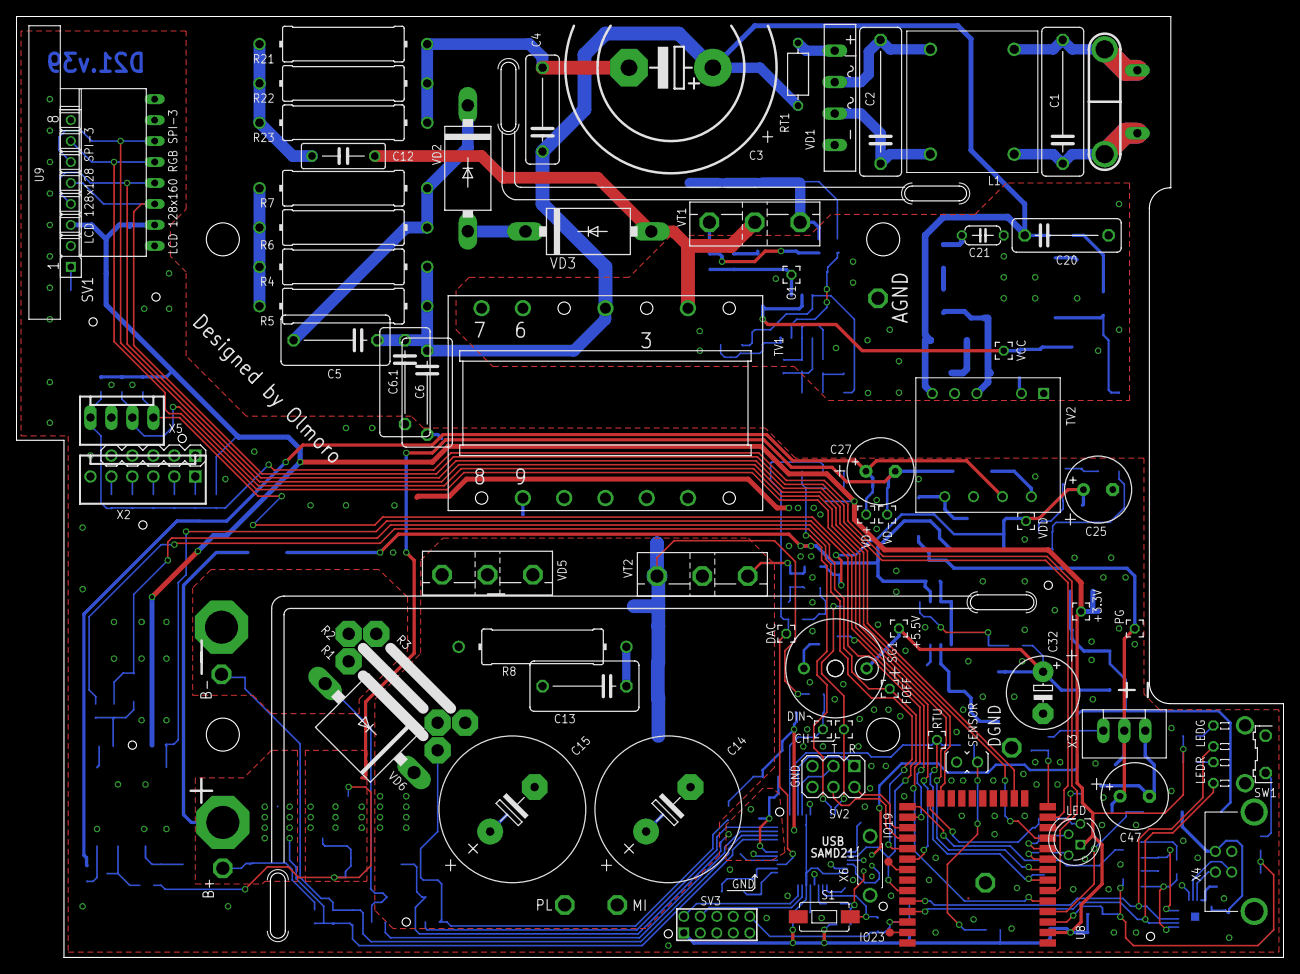
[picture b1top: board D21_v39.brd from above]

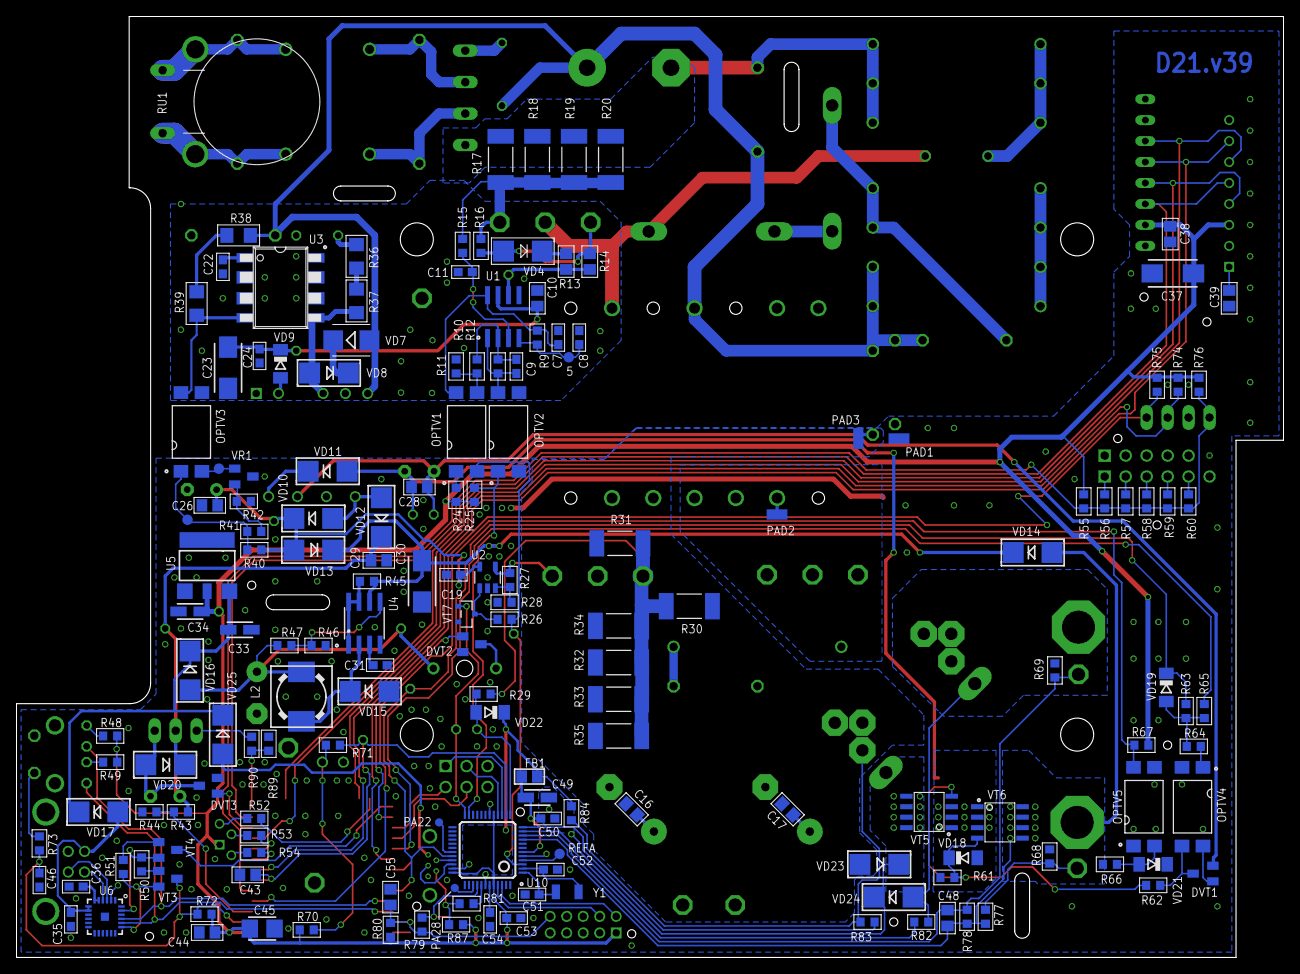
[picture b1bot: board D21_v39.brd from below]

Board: 2 copper layers, 153.5 x 114.0 mm, 250 parts (165 on the bottom side), 144 nets.

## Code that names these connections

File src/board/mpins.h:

#ifndef _MPINS_H_
#define _MPINS_H_
/*
* https://github.com/BLavery/SAMD21-M0-Mini
* select the board: Tools/Board = Arduino SAMD / "Arduino Zero (Native USB Port)".
* Double-click the board reset button. Upload. See if a LED blinks.
* explain a bit:
* 1. The Arduino bootloader uses double click on reset button to enter flash upload mode. Single
*    reset enters normal running mode. (Boot0/1 jumpers, like STM32 uses, are not used on the SAMD.)
* 2. The serial/bossac mode of USB upload is included in the Arduino install.
* 3. The regular user LED is missing. So we choose one of the TX/RX LEDs. For the moment, 
*    the Arduino sketch is NOT otherwise driving these as TX/RX indicators (see above), 
*    so we can re-employ them.
* 4. But what pin or GPIO number? For this board, reference the pins as 0-26 or A0-A5. Not D25, 
*    nor PB03 or PB3.
*
* https://github.com/arduino/ArduinoCore-samd/pull/374/files
* additional analog inputs: A6-A11 #374 
*/

//#include "SAMD_AnalogCorrection.h"
#include "stdint.h"

namespace MPins
{

//#include <Arduino.h>

//                q920_name      arduino_pin  M0-MINI   SAMD21_name
constexpr uint8_t uart_rx           =    0;    // D0   PA11/UART-RX             
constexpr uint8_t uart_tx           =    1;    // D1   PA10/UART-TX  
constexpr uint8_t off_pin           =    2;    // D4   PA14
constexpr uint8_t d3_pin            =    3;    // D3   PA09
constexpr uint8_t rtu_pin           =   50;    // D3   additional analog as PA09
constexpr uint8_t rtu_mux           =    9;    // D3   additional analog as PA09
constexpr uint8_t d2_pin            =    4;    // D2   PA08 nu
constexpr uint8_t din_pin           =   51;    // D2   additional analog as PA08
constexpr uint8_t din_mux           =    8;    // D2   additional analog as PA08
constexpr uint8_t ch_pin            =    5;    // D5   PA15
constexpr uint8_t d8_pin            =    8;    // D8   PA06 nu
constexpr uint8_t d9_pin            =    9;    // D9   PA07 nu

constexpr uint8_t shunt_plus_pin    =   46;    // D8   additional analog as PA06
constexpr uint8_t shunt_minus_pin   =   47;    // D9   additional analog as PA07
constexpr uint8_t shunt_plus_mux    =    6;    // D8   additional analog as PA06
constexpr uint8_t shunt_minus_mux   =    7;    // D9   additional analog as PA07

constexpr uint8_t ss_pin            =   10;    // D10  PA18
constexpr uint8_t mosi_pin          =   11;    // D11  PA16
constexpr uint8_t miso_pin          =   12;    // D12  PA19
constexpr uint8_t sck_pin           =   13;    // D13  PA17

constexpr uint8_t dac_pin           =   14;    // A0   PA02
constexpr uint8_t bat_plus_pin      =   17;    // A3   PA04
constexpr uint8_t bat_minus_pin     =   18;    // A4   PA05
constexpr uint8_t bat_plus_mux      =    4;    // A3   PA04
constexpr uint8_t bat_minus_mux     =    5;    // A4   PA05
constexpr uint8_t icsp_miso         =   22;    //  1   PA12/MISO ICSP  !! На схеме 2
constexpr uint8_t icsp_mosi         =   23;    //  4   PB10/MOSI ICSP              3
constexpr uint8_t icsp_sck          =   24;    //  3   PB11/SCK  ICSP              4
constexpr uint8_t led_rx            =   25;    // no   PB03/LED1 (LED_BUILTIN, LED_RX)
constexpr uint8_t led_tx            =   26;    // no   PA27/LED2 (LED_TX)
constexpr uint8_t foff_pin          =   21;    // D21  PA23

// Not used
//    6    // D6   PA20       // d21
//    7    // D7   PA21       // d21
//   15    // A1   PB08       // d21
//   16    // A2   PB09       // d21
//   19    // A5   PB02       // d21
//   20    // D20  PA22/SDA
//   21    // D21  PA23/SCL

};

#endif // !_MPINS_H_

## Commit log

2020-04-16 Передача пакета
2020-04-17 +PID
2020-04-18 ПИД commands
2020-04-18 +ADC
2020-04-23 Info, Echo - OK
2020-04-23 CMD_PID
2020-04-25 PID-TEST
2020-04-25 PID commands
2020-04-27 README
2020-04-28 Read probes
2020-04-29 ADC commands
2020-04-30 COMMAND 52
2020-05-05 adc comm 50 51 52
2020-05-10 Optimization
2020-05-10 comm 55 - 57
2020-05-13 Celsius
2020-05-17 State1, 2
2020-05-18 State
2020-05-18 Команды управления процессами
2020-05-18 Commands 60 ...
2020-05-19 DAC control
2020-05-19 command 62
2020-05-20 Оптимизация
2020-05-21 PID-control
2020-05-22 PID control
2020-05-23 PID-U
2020-05-27 PCB new
2020-05-29 Docs
2020-06-05 Nothi

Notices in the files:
parts and their libraries:
microbuilder_v2: This work is placed in the public domain, and may be freely used for commercial and non-commercial work with the following conditions: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
esp32: Creative Commons Attribution-ShareAlike 4.0 International
